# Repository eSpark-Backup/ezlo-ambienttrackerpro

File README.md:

# ezlo-ambienttrackerpro
Convert and do corrections in Ambient Tracker Pro design

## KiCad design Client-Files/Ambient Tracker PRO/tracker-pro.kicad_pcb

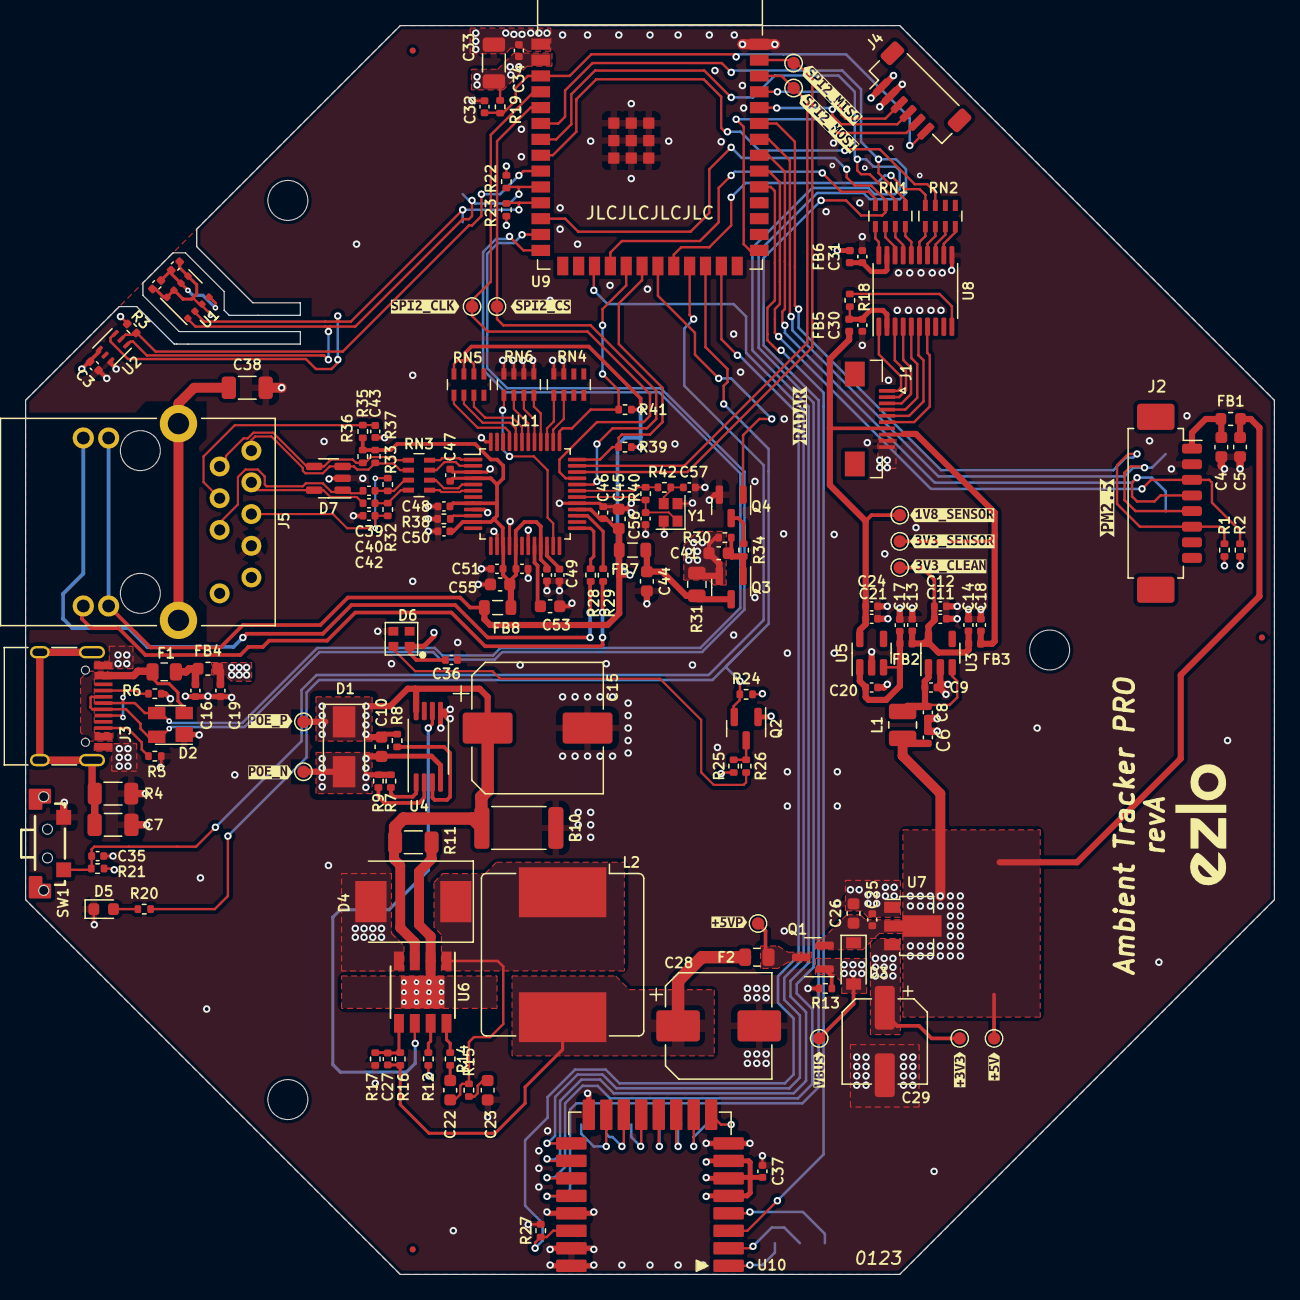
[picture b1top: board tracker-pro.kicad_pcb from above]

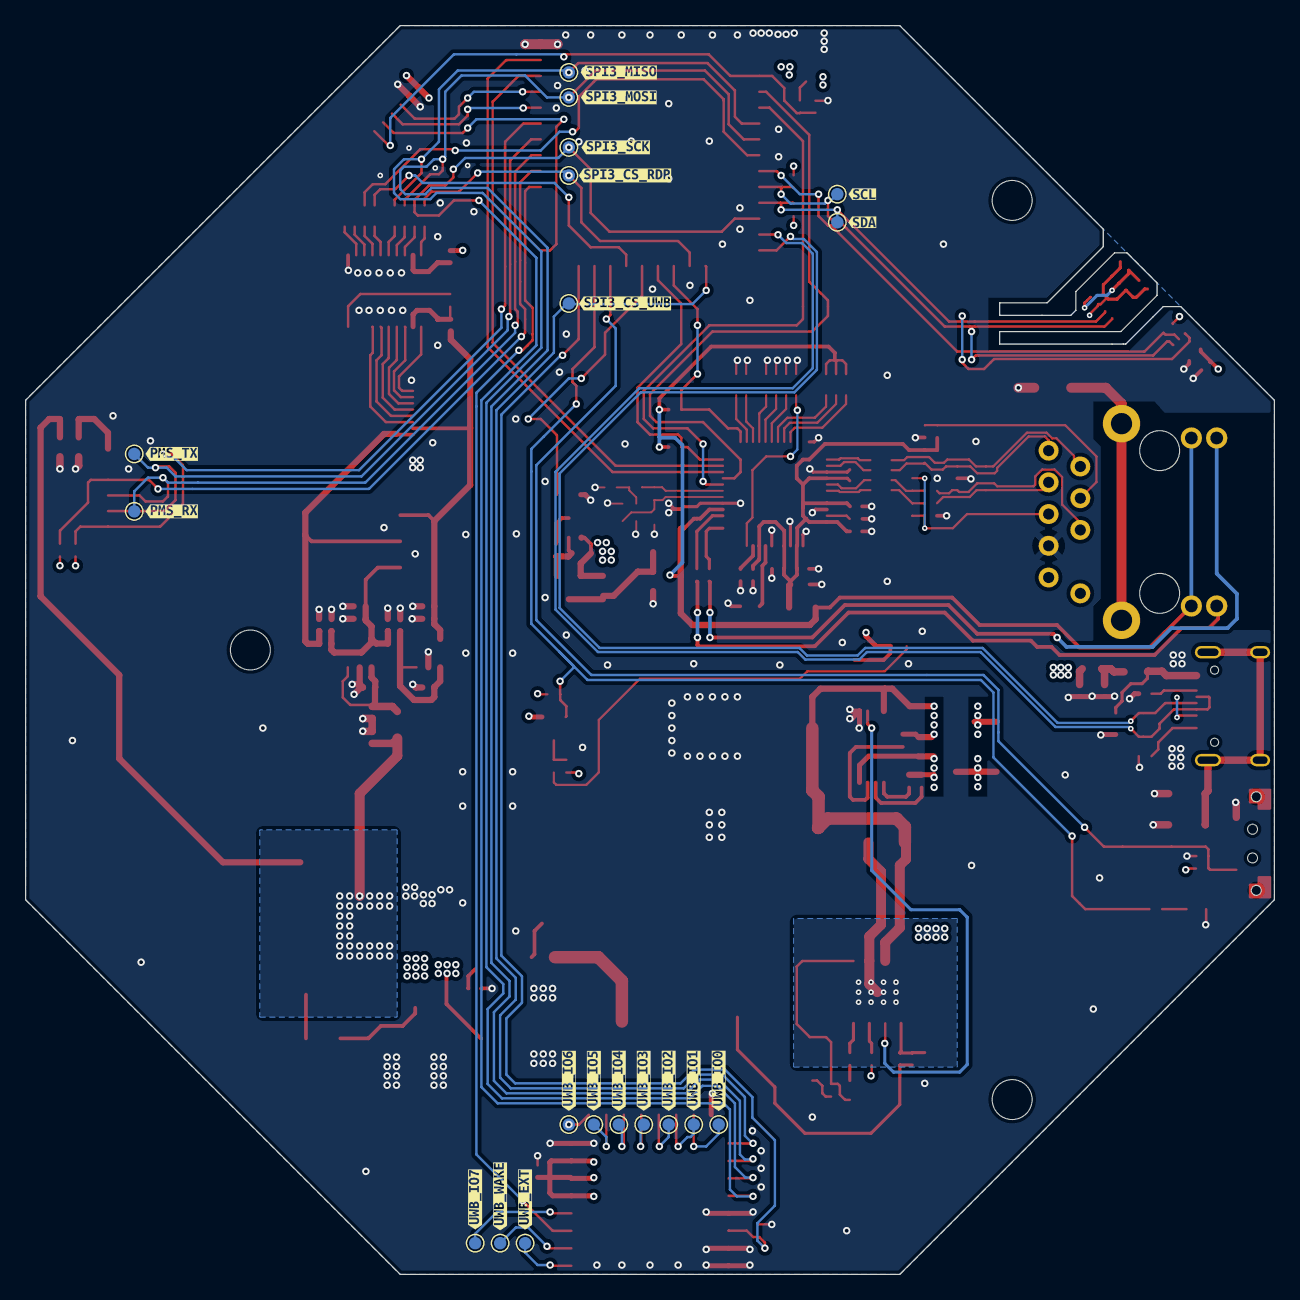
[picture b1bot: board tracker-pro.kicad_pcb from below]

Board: 4 copper layers, 100.0 x 100.0 mm, 220 parts (38 on the bottom side), 128 nets.

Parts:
C1, C2, C9, C11, C13, C14, C18, C19, C20, C21, C25, C30, C31, C34, C35, C36, C37, C46, C47, C48, C50, C51, C52, C54: 0.1uF; C_0402_1005Metric
C3, C32: 1uF; C_0402_1005Metric
C4, C5, C26, C45, C55: 10uF; C_0603_1608Metric
C6, C8, C12, C17, C24: 10uF; C_0402_1005Metric
C7: 4.7nF; C_1206_3216Metric
C10, C22: 0.1uF; C_0603_1608Metric
C15: 15uF; CP_Elec_10x10
C16: 0.01uF; C_0402_1005Metric
C23: 220pF; C_0603_1608Metric
C27, C56, C57: 12pF; C_0402_1005Metric
C28: 470uF; CP_Elec_8x10
C29: 100uF; CP_Elec_6.3x5.8
C33: 22uF; C_1206_3216Metric
C38: 1nF 2KV X7R; C_1206_3216Metric
C39, C40: 6.8nF; C_0402_1005Metric
C41, C44: 22uF; C_0603_1608Metric
C42, C49: 10nF; C_0402_1005Metric
C43: 22nF; C_0402_1005Metric
C53: 4.7uF; C_0603_1608Metric
D1: SMAJ58A; D_SMA
D2: SP0503BAHT; SOT-143
D3: PMEG4030ER; D_SOD-123
D4: SS510; D_SMC
D5: LED_GREEN; LED_0603_1608Metric
D6: SK6812-EC20; sk6812-2020
D7: SP0504BAHT; SOT-23-5
F1, F2: 1A; Fuse_0805_2012Metric
FB1, FB4: BLM18SG121TN1D; L_0603_1608Metric
FB2, FB3, FB5, FB6: BLM15PD121SN1B; L_0402_1005Metric
FB7, FB8: 600R 3A; L_0805_2012Metric
FID1, FID2, FID3: Fiducial; Fiducial_0.5mm_Mask1mm
H1, H2, H3: MountingHole; MountingHole_3.2mm_M3_DIN965
J1: Conn_01x10; AFC01-S10FCC-00_1x10_P0.5mm_Horizontal
J2: PMS5003; Molex_PicoBlade_53261-0871_1x08-1MP_P1.25mm_Horizontal
J3: USB_C_Receptacle_USB2.0; USB_C_Receptacle_HRO_TYPE-C-31-M-12
J4: VoltLink_target; VoltLink-vertical
J5: HanRun_HR873170C
L1: 10uH; L_1008_2520Metric
L2: 33uH 2A; L_Bourns_SRR1208_12.7x12.7mm
N1: Housing; ambient_tracker_pro_revA_enclosure
Q1: SI2323DS; SOT-23
Q2: Si2302CDS; SOT-23
Q3: WPM2015-3; SOT-23
Q4: LMUN2211LT1G; SOT-23
R1, R2, R3, R12, R19, R21, R24, R25, R30, R39, R41: 10K; R_0402_1005Metric
R4: 1M; R_1206_3216Metric
R5, R6: 5K1; R_0402_1005Metric
R7: 180K; R_0402_1005Metric
R8: 24K9; R_0402_1005Metric
R9: 4K42; R_0402_1005Metric
R10: 4K7; R_2512_6332Metric
R11: 0.03R; R_1206_3216Metric
R13, R27: 100K; R_0402_1005Metric
R14: 4R7; R_0402_1005Metric
R15: 22R; R_0402_1005Metric
R16: 300K; R_0402_1005Metric
R17: 57K1; R_0402_1005Metric
R18, R42: 0R; R_0402_1005Metric
R20, R26, R34: 1K; R_0402_1005Metric
R22, R23: 4K7; R_0402_1005Metric
R28, R29: 330R; R_0402_1005Metric
R31: 0R; R_0805_2012Metric
R32, R33, R36, R37: 49R9; R_0402_1005Metric
R35: 10R; R_0402_1005Metric
R38: 12K4; R_0402_1005Metric
R40: 1M; R_0402_1005Metric
RN1, RN2: 0R; R_Array_Concave_4x0603
RN3: 33R; R_Array_Concave_4x0603
RN4, RN5, RN6: 10K; R_Array_Concave_4x0603
SW1: USER; Switch_YTS-B003-2A
TP1: PMS_TX; TestPoint_Pad_D1.0mm
TP2: PMS_RX; TestPoint_Pad_D1.0mm
TP3: POE_P; TestPoint_Pad_D1.0mm
TP4: POE_N; TestPoint_Pad_D1.0mm
TP5: 3V3_C; TestPoint_Pad_D1.0mm
TP6: 3V3_S; TestPoint_Pad_D1.0mm
TP7: VBUS; TestPoint_Pad_D1.0mm
TP8: 1V8_S; TestPoint_Pad_D1.0mm
TP9: +5V; TestPoint_Pad_D1.0mm
TP10: 3V3; TestPoint_Pad_D1.0mm
TP11: 5VP; TestPoint_Pad_D1.0mm
TP12: SCL; TestPoint_Pad_D1.0mm
TP13: SDA; TestPoint_Pad_D1.0mm
TP14: SPI2_MISO; TestPoint_Pad_D1.0mm
TP15: SPI2_MOSI; TestPoint_Pad_D1.0mm
TP16: SPI2_SCK; TestPoint_Pad_D1.0mm
TP17: SPI2_CS; TestPoint_Pad_D1.0mm
TP18: SPI3_MISO; TestPoint_Pad_D1.0mm
TP19: SPI3_MOSI; TestPoint_Pad_D1.0mm
TP20: SPI3_SCK; TestPoint_Pad_D1.0mm
TP21: SPI3_CS_UWB; TestPoint_Pad_D1.0mm
TP22: SPI3_CS_RDR; TestPoint_Pad_D1.0mm
TP23: UWB_EXT; TestPoint_Pad_D1.0mm
TP24: UWB_WAKE; TestPoint_Pad_D1.0mm
TP25: UWB_IO7; TestPoint_Pad_D1.0mm
TP26: UWB_IO6; TestPoint_Pad_D1.0mm
TP27: UWB_IO5; TestPoint_Pad_D1.0mm
TP28: UWB_IO4; TestPoint_Pad_D1.0mm
TP29: UWB_IO3; TestPoint_Pad_D1.0mm
TP30: UWB_IO2; TestPoint_Pad_D1.0mm
TP31: UWB_IO1; TestPoint_Pad_D1.0mm
TP32: UWB_IO0; TestPoint_Pad_D1.0mm
U1: BME680; Bosch_LGA-8_3x3mm_P0.8mm_ClockwisePinNumbering
U2: LTR-303ALS-01; Lite-On_LTR-303ALS-01
U3: XC6228D332VR-G; SOT-23-5
U4: TPS2375PW-1; TSSOP-8_4.4x3mm_P0.65mm
U5: XC6228D182VR-G; SOT-23-5
U6: TX4138; Diodes_SO-8EP
U7: LR1107; SOT-89-3
U8: TXS0108EPWR; TSSOP-20_4.4x6.5mm_P0.65mm
U9: ESP32-S3-WROOM-1-N8R2; ESP32-S3-WROOM-1
U10: DWM3000; Qorvo_DWM3000
U11: W5500; LQFP-48_7x7mm_P0.5mm
V1: EZLO_LOGO; Logo Ezlo_M
Y1: 25Mhz; Crystal_SMD_2016-4Pin_2.0x1.6mm
kibuzzard-63AACF69: G***; kibuzzard-63AACF69
kibuzzard-63AACF76: G***; kibuzzard-63AACF76
kibuzzard-63AACFD0: G***; kibuzzard-63AACFD0
kibuzzard-63AAD0AA: G***; kibuzzard-63AAD0AA
kibuzzard-63AAD00B: G***; kibuzzard-63AAD00B
kibuzzard-63AAD0BE: G***; kibuzzard-63AAD0BE
kibuzzard-63AAD0D4: G***; kibuzzard-63AAD0D4
kibuzzard-63AAD0DC: G***; kibuzzard-63AAD0DC
kibuzzard-63AAD001: G***; kibuzzard-63AAD001
kibuzzard-63AAD1C0: G***; kibuzzard-63AAD1C0
kibuzzard-63AAD1D3: G***; kibuzzard-63AAD1D3
kibuzzard-63AAD1FD: G***; kibuzzard-63AAD1FD
kibuzzard-63AAD2A3: G***; kibuzzard-63AAD2A3
kibuzzard-63AAD2C0: G***; kibuzzard-63AAD2C0
kibuzzard-63AAD2D7: G***; kibuzzard-63AAD2D7
kibuzzard-63AAD02E: G***; kibuzzard-63AAD02E
kibuzzard-63AAD07E: G***; kibuzzard-63AAD07E
kibuzzard-63AAD16B: G***; kibuzzard-63AAD16B
kibuzzard-63AAD19E: G***; kibuzzard-63AAD19E
kibuzzard-63AAD20D: G***; kibuzzard-63AAD20D
kibuzzard-63AAD21C: G***; kibuzzard-63AAD21C
kibuzzard-63AAD27D: G***; kibuzzard-63AAD27D
kibuzzard-63AAD32F: G***; kibuzzard-63AAD32F
kibuzzard-63AAD33F: G***; kibuzzard-63AAD33F
kibuzzard-63AAD039: G***; kibuzzard-63AAD039
kibuzzard-63AAD045: G***; kibuzzard-63AAD045
kibuzzard-63AAD061: G***; kibuzzard-63AAD061
kibuzzard-63AAD088: G***; kibuzzard-63AAD088
kibuzzard-63AAD273: G***; kibuzzard-63AAD273
kibuzzard-63AAD309: G***; kibuzzard-63AAD309
kibuzzard-63AAD314: G***; kibuzzard-63AAD314
kibuzzard-63AAD337: G***; kibuzzard-63AAD337
kibuzzard-63AAD348: G***; kibuzzard-63AAD348
kibuzzard-63AAD350: G***; kibuzzard-63AAD350

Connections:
1V8_SENSOR: C21.1, C24.1, FB5.2, J1.7, TP8.1, U5.5 (VOUT)
3V3_SENSOR: C18.1, FB3.2, J1.8, TP6.1
+3V3: C1.2, C2.1, C3.1, C29.1, C33.2, C34.2, C37.1, C41.1, FB6.1, J4.1 (3V3), Q2.1 (G), Q3.2 (S), R1.1, R2.1, R3.1, R12.2, R19.2, R21.2, R22.2, R23.2, R24.1, R30.2, R31.1, TP10.1, U1.2 (CSB), U1.5 (SDO), U1.6 (VDDIO), U1.8 (VDD), U2.1 (VDD), U7.3 (VOUT), U9.2 (3V3), U10.5 (VDD1), U10.6 (VDD3V3), U10.7 (VDD3V3)
+5V: C5.1, C6.1, C25.1, C26.1, C36.1, D3.1 (K), D6.1 (VDD), FB1.2, L1.1, Q1.2 (S), R25.1, TP9.1, U7.2 (VIN)
+5VP: F2.1, Q1.3 (D), TP11.1
/ESP32/DIN1: D6.4 (DIN), R26.2
/ESP32/EN: C32.1, J4.6 (EN), R19.1, U9.3 (EN)
/ESP32/GPIO13: Q4.1 (B), U9.21 (GPIO13)
/ESP32/GPIO14: RN2.4 (R4.1), U9.22 (GPIO14)
/ESP32/GPIO15: RN2.3 (R3.1), U9.8 (GPIO15)
/ESP32/GPIO21: C35.1, R21.1, SW1.1, U9.23 (GPIO21)
/ESP32/GPIO47: Q2.2 (S), R20.1, R24.2, U9.24 (GPIO47)
/ESP32/IO0: J4.5 (IO0), U9.27 (GPIO0/BOOT)
/ESP32/RXD: J4.4 (RXD), U9.36 (U0RXD/GPIO44)
/ESP32/SCL: R22.1, TP12.1, U1.4 (SCK), U2.4 (SCL), U9.10 (GPIO17)
/ESP32/SDA: R23.1, TP13.1, U1.3 (SDI), U2.6 (SDA), U9.11 (GPIO18)
/ESP32/SPI2_CS: TP17.1, U9.5 (GPIO5), U11.32 (~SCS)
/ESP32/SPI2_MISO: TP14.1, U9.39 (GPIO1), U11.34 (MISO)
/ESP32/SPI2_MOSI: TP15.1, U9.38 (GPIO2), U11.35 (MOSI)
/ESP32/SPI2_SCK: TP16.1, U9.4 (GPIO4), U11.33 (SCLK)
/ESP32/SPI3_CS_RDR: RN1.4 (R4.1), TP22.1, U9.18 (GPIO10)
/ESP32/SPI3_CS_UWB: TP21.1, U9.17 (GPIO9), U10.17 (CS)
/ESP32/SPI3_MISO: RN1.1 (R1.1), TP18.1, U9.6 (GPIO6), U10.19 (MISO)
/ESP32/SPI3_MOSI: RN1.2 (R2.1), TP19.1, U9.7 (GPIO7), U10.18 (MOSI)
/ESP32/SPI3_SCK: RN1.3 (R3.1), TP20.1, U9.12 (GPIO8), U10.20 (SCLK)
/ESP32/TXD: J4.3 (TXD), U9.37 (U0TXD/GPIO43)
/Ethernet/1V2O: C49.1, U11.22 (1V2O)
/Ethernet/ACTLED: R29.2, U11.27 (ACTLED)
/Ethernet/EXRES1: R38.2, U11.10 (EXRES1)
/Ethernet/LAN_ACT: J5.14, R29.1
/Ethernet/LAN_CT_R: C42.1, J5.5, R32.2, R33.2
/Ethernet/LAN_CT_T: C43.1, J5.4, R35.2
/Ethernet/LAN_LINK: J5.12, R28.1
/Ethernet/LAN_PWR_N: C10.2, D1.2 (A), J5.10, R7.2, R9.2, TP4.1, U4.4 (VSS)
/Ethernet/LAN_RD_N: C39.1, D7.1 (K), J5.6
/Ethernet/LAN_RD_P: C40.1, D7.5 (K), J5.3
/Ethernet/LAN_TD_N: D7.4 (K), J5.2, R36.2, RN3.5 (R4.2)
/Ethernet/LAN_TD_P: D7.3 (K), J5.1, R37.2, RN3.6 (R3.2)
/Ethernet/LINKLED: R28.2, U11.25 (LINKLED)
/Ethernet/PMODE0: RN5.1 (R1.1), U11.45 (PMODE0)
/Ethernet/PMODE1: RN5.2 (R2.1), U11.44 (PMODE1)
/Ethernet/PMODE2: RN5.3 (R3.1), U11.43 (PMODE2)
/Ethernet/RJ45_SHIELD: C38.1, J5.15 (SHIELD), J5.16 (SHIELD)
/Ethernet/TOCAP: C53.1, U11.20 (TOCAP)
/Ethernet/W5500_3V3: C44.1, FB7.1, Q3.3 (D), R31.2
/Ethernet/W5500_INT: R39.1, U9.20 (GPIO12), U11.36 (~INT)
/Ethernet/W5500_RST: R41.1, U9.19 (GPIO11), U11.37 (~RST)
/Ethernet/W5500_RX_N: RN3.2 (R2.1), U11.5 (RXN)
/Ethernet/W5500_RX_P: RN3.1 (R1.1), U11.6 (RXP)
/Ethernet/W5500_TX_N: RN3.4 (R4.1), U11.1 (TXN)
/Ethernet/W5500_TX_P: RN3.3 (R3.1), U11.2 (TXP)
/Ethernet/W5500_XI: C56.1, R40.1, U11.30 (XI/CLKIN), Y1.1
/Ethernet/W5500_XO: R40.2, R42.2, U11.31 (XO)
/Level shifter/SPI_OE: R18.1, U8.10 (OE)
/Level shifter/VCCA: C30.1, FB5.1, R18.2, U8.2 (VCCA)
/Level shifter/VCCB: C31.1, FB6.2, U8.19 (VCCB)
/Power-Interface/3V3_CLEAN: C11.1, C12.1, C13.1, C14.1, FB2.1, FB3.1, TP5.1, U3.5 (VOUT)
/Power-Interface/3V3_LDO1V8: C17.1, C20.1, FB2.2, U5.1 (VIN), U5.3 (CE)
/Power-Interface/CC1: J3.A5 (CC1), R6.1
/Power-Interface/CC2: J3.B5 (CC2), R5.1
/Power-Interface/DCDC_BS: R14.2, U6.8 (BS)
/Power-Interface/DCDC_FB: C27.2, R16.1, R17.2, U6.5 (FB)
/Power-Interface/DCDC_ILIM: R11.1, U6.2 (ILIM), U6.9 (ILIM)
/Power-Interface/DCDC_OUT: C27.1, C28.1, F2.2, L2.2, R16.2
/Power-Interface/DCDC_POK: R12.1, U6.7 (POK)
/Power-Interface/DCDC_SW: C22.2, D4.1 (K), L2.1, R15.2, U6.1 (SW)
/Power-Interface/DCDC_VIN: C10.1, C15.1, D1.1 (K), J5.9, R8.1, R10.2, R11.2, TP3.1, U4.8 (VDD), U6.3 (VIN)
/Power-Interface/POE_EN_DCDC: U4.6 (PG), U6.6 (EN)
/Power-Interface/USB_D_N: D2.4 (K), J3.A7 (D-), J3.B7 (D-), U9.13 (GPIO19/USB_D-)
/Power-Interface/USB_D_P: D2.3 (K), J3.A6 (D+), J3.B6 (D+), U9.14 (GPIO20/USB_D+)
/Power-Interface/VIN_CLEAN: C8.1, C9.1, L1.2, U3.1 (VIN), U3.3 (CE)
/Power-Interface/V_USB: D2.2 (K), F1.2, J3.A4 (VBUS), J3.A9 (VBUS), J3.B4 (VBUS), J3.B9 (VBUS)
/Sensors/BGT_CLK: J1.2, U8.3 (A2)
/Sensors/BGT_CS: J1.1, U8.1 (A1)
/Sensors/BGT_IRQ: J1.6, U8.7 (A6)
/Sensors/BGT_MISO: J1.4, U8.5 (A4)
/Sensors/BGT_MOSI: J1.3, U8.4 (A3)
/Sensors/BGT_RST: J1.5, U8.6 (A5)
/Sensors/INT_ALS: R3.2, U2.5 (INT), U9.9 (GPIO16)
/Sensors/PMS_5V: C4.1, FB1.1, J2.1
/Sensors/PMS_RST: J2.6, R1.2, U9.35 (TMS/GPIO42)
/Sensors/PMS_RX: J2.4, TP2.1, U9.33 (TDO/GPIO40)
/Sensors/PMS_SET: J2.3, R2.2, U9.32 (TCK/GPIO39)
/Sensors/PMS_TX: J2.5, TP1.1, U9.34 (TDI/GPIO41)
/UWB/UWB_IRQ: R27.1, U9.25 (GPIO48), U10.22 (IO8/IRQ)
/UWB/UWB_RST: U9.31 (GPIO38), U10.3 (~RST)
GND: C1.1, C2.2, C3.2, C4.2, C5.2, C6.2, C7.2, C8.2, C9.2, C11.2, C12.2, C13.2, C14.2, C15.2, C16.2, C17.2, C18.2, C19.2, C20.2, C21.2, C23.1, C24.2, C25.2, C26.2, C28.2, C29.2, C30.2, C31.2, C32.2, C33.1, C34.1, C35.2, C36.2, C37.2, C38.2, C42.2, C43.2, C44.2, C45.2, C46.2, C47.2, C48.2, C49.2, C50.2, C51.2, C52.2, C53.2, C54.2, C55.2, C56.2, C57.2, D2.1 (A), D4.2 (A), D5.1 (K), D6.3 (VSS), D7.2 (A), J1.9, J1.10, J2.2, J3.A1 (GND), J3.A12 (GND), J3.B1 (GND), J3.B12 (GND), J4.2 (GND), J5.7, Q4.2 (E), R4.2, R5.2, R6.2, R10.1, R13.2, R17.1, R27.2, R38.1, RN4.3 (R3.1), RN4.4 (R4.1), RN6.1 (R1.1), RN6.2 (R2.1), RN6.3 (R3.1), RN6.4 (R4.1), SW1.2, U1.1 (GND), U1.7 (GND), U2.3 (GND), U3.2 (GND), U4.5 (RTN), U5.2 (GND), U6.4 (GND), U7.1 (GND), U8.11 (GND), U9.1 (GND), U9.40 (GND), U9.41 (GND), U10.8 (GND), U10.16 (GND), U10.21 (GND), U10.23 (GND), U10.24 (GND), U11.3 (AGND), U11.9 (AGND), U11.14 (AGND), U11.16 (AGND), U11.19 (AGND), U11.29 (GND), U11.48 (AGND), Y1.2, Y1.4
unnamed: C7.1, J3.S1 (SHIELD), R4.1
unnamed: C16.1, F1.1, FB4.1
unnamed: C22.1, R14.1
unnamed: C23.2, R15.1
unnamed: C39.2, R33.1, RN3.7 (R2.2)
unnamed: C40.2, R32.1, RN3.8 (R1.2)
unnamed: C41.2, Q3.1 (G), R30.1, R34.1
unnamed: C57.1, R42.1, Y1.3
unnamed: D5.2 (A), R20.2
unnamed: Q2.3 (D), R25.2, R26.1
unnamed: Q4.3 (C), R34.2
unnamed: R7.1, U4.1 (ILIM)
unnamed: R8.2, U4.3 (DET)
unnamed: R9.1, U4.2 (CLASS)
unnamed: RN1.5 (R4.2), U8.20 (B1)
unnamed: RN1.6 (R3.2), U8.18 (B2)
unnamed: RN1.7 (R2.2), U8.17 (B3)
unnamed: RN1.8 (R1.2), U8.16 (B4)
unnamed: RN2.5 (R4.2), U8.15 (B5)
unnamed: RN2.6 (R3.2), U8.14 (B6)
unnamed: RN2.7 (R2.2), U8.13 (B7)
unnamed: RN2.8 (R1.2), U8.12 (B8)
unnamed: RN4.5 (R4.2), U11.39 (RSVD)
unnamed: RN4.6 (R3.2), U11.38 (RSVD)
unnamed: RN6.5 (R4.2), U11.23 (RSVD)
unnamed: RN6.6 (R3.2), U11.42 (RSVD)
unnamed: RN6.7 (R2.2), U11.41 (RSVD)
unnamed: RN6.8 (R1.2), U11.40 (RSVD)
unnamed: TP23.1, U10.1 (EXTON)
unnamed: TP24.1, U10.2 (WAKEUP)
unnamed: TP25.1, U10.4 (IO7/SYNC)
unnamed: TP26.1, U10.9 (IO6/SPIPHA)
unnamed: TP27.1, U10.10 (IO5/SPIPOL)
unnamed: TP28.1, U10.11 (IO4)
unnamed: TP29.1, U10.12 (IO3/TXLED)
unnamed: TP30.1, U10.13 (IO2/RXLED)
unnamed: TP31.1, U10.14 (IO1/SFDLED)
unnamed: TP32.1, U10.15 (IO0/RXOKLED)
VBUS: C19.1, D3.2 (A), FB4.2, Q1.1 (G), R13.1, TP7.1
VDD: C45.1, C46.1, FB7.2, FB8.1, J5.11, J5.13, R39.2, R41.2, RN5.6 (R3.2), RN5.7 (R2.2), RN5.8 (R1.2), U11.28 (VDD)
VDDA: C47.1, C48.1, C50.1, C51.1, C52.1, C54.1, C55.1, FB8.2, R35.1, R36.1, R37.1, U11.4 (AVDD), U11.8 (AVDD), U11.11 (AVDD), U11.15 (AVDD), U11.17 (AVDD), U11.21 (AVDD)

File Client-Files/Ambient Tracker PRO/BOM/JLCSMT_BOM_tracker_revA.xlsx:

Comment | Designator | Footprint | LCSC Part #（optional）
0.1uF | C1, C2, C9, C11, C13, C14, C16, C18, C19, C20, C21, C25, C30, C31, C34, C35, C3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 | Capacitor_SMD:C_0402_1005Metric | C307331
1uF | C3, C32, | Capacitor_SMD:C_0402_1005Metric | C52923
10uF | C4, C5, C26, C45, C55, | Capacitor_SMD:C_0603_1608Metric | C92487
10uF | C6, C8, C12, C17, C24, | Capacitor_SMD:C_0402_1005Metric | C315248
4.7nF | C7, | Capacitor_SMD:C_1206_3216Metric | C107198
0.1uF | C10, C22, | Capacitor_SMD:C_0603_1608Metric | C15725
15uF | C15, | Capacitor_SMD:CP_Elec_10x10 | C473415
220pF | C23, | Capacitor_SMD:C_0603_1608Metric | DNP | C472787
12pF | C27, C56, C57, | Capacitor_SMD:C_0402_1005Metric | C1547
470uF | C28, | Capacitor_SMD:CP_Elec_8x10 | C164069
100uF | C29, | Capacitor_SMD:CP_Elec_6.3x5.8 | C340720
22uF | C33, | Capacitor_SMD:C_1206_3216Metric | C408152
1nF 2KV X7R | C38, | Capacitor_SMD:C_1206_3216Metric | C23631
6.8nF | C39, C40, | Capacitor_SMD:C_0402_1005Metric | C307331
22uF | C41, C44, | Capacitor_SMD:C_0603_1608Metric | C59461
10nF | C42, C49, | Capacitor_SMD:C_0402_1005Metric | C307331
22nF | C43, | Capacitor_SMD:C_0402_1005Metric | C307331
4.7uF | C53, | Capacitor_SMD:C_0603_1608Metric | C19666
SMAJ58A | D1, | Diode_SMD:D_SMA | C320541
SP0503BAHT | D2, | Package_TO_SOT_SMD:SOT-143 | C2682275
PMEG4030ER | D3, | Diode_SMD:D_SOD-123 | C389355
SS510 | D4, | Diode_SMD:D_SMC | C717458
LED_GREEN | D5, | LED_SMD:LED_0603_1608Metric | C84267
SK6812-EC20 | D6, | Ezlo:sk6812-2020 | C2909058
SP0504BAHT | D7, | Package_TO_SOT_SMD:SOT-23-5 | C2827708
1A | F1, F2, | Fuse:Fuse_0805_2012Metric | C369152
BLM18SG121TN1D | FB1, FB4, | Inductor_SMD:L_0603_1608Metric | C113030
BLM15PD121SN1B | FB2, FB3, FB5, FB6, | Inductor_SMD:L_0402_1005Metric | C76891
600R 3A | FB7, FB8, | Inductor_SMD:L_0805_2012Metric | C139168
Conn_01x10 | J1, | Ezlo:AFC01-S10FCC-00_1x10_P0.5mm_Horizontal | C262266
USB_C_Receptacle_USB2.0 | J3, | Ezlo:USB_C_Receptacle_HRO_TYPE-C-31-M-12 | C165948
VoltLink_target | J4, | Voltlog:VoltLink-vertical | C145963
10uH | L1, | Inductor_SMD:L_1008_2520Metric | C88532
33uH 2A | L2, | Inductor_SMD:L_Bourns_SRR1208_12.7x12.7mm | C2929502
SI2323DS | Q1, | Package_TO_SOT_SMD:SOT-23 | C693130
Si2302CDS | Q2, | Package_TO_SOT_SMD:SOT-23 | C10488
WPM2015-3 | Q3, | Package_TO_SOT_SMD:SOT-23 | C5246393
LMUN2211LT1G | Q4, | Package_TO_SOT_SMD:SOT-23 | C12775
10K | R1, R2, R3, R12, R19, R21, R24, R25, R30, R39, R41, | Resistor_SMD:R_0402_1005Metric | C25744
1M | R4, | Resistor_SMD:R_1206_3216Metric | C17927
5K1 | R5, R6, | Resistor_SMD:R_0402_1005Metric | C25905
180K | R7, | Resistor_SMD:R_0402_1005Metric | C284388
24K9 | R8, | Resistor_SMD:R_0402_1005Metric | C25874
4K42 | R9, | Resistor_SMD:R_0402_1005Metric | C517779
4K7 | R10, | Resistor_SMD:R_2512_6332Metric | C473645
0.03R | R11, | Resistor_SMD:R_1206_3216Metric | C473665
100K | R13, R27, | Resistor_SMD:R_0402_1005Metric | C25741
4R7 | R14, | Resistor_SMD:R_0402_1005Metric | C25169
22R | R15, | Resistor_SMD:R_0402_1005Metric | DNP | C25092
301K | R16, | Resistor_SMD:R_0402_1005Metric | C226978
57K6 | R17, | Resistor_SMD:R_0402_1005Metric | C26983
0R | R18, R42, | Resistor_SMD:R_0402_1005Metric | C17168
1K | R26, R34, | Resistor_SMD:R_0402_1005Metric | C25905
1K | R20 | Resistor_SMD:R_0402_1005Metric | DNP
4K7 | R22, R23, | Resistor_SMD:R_0402_1005Metric | C25900
330R | R28, R29, | Resistor_SMD:R_0402_1005Metric | C25104
0R | R31, | Resistor_SMD:R_0805_2012Metric | DNP | C17477
49R9 | R32, R33, R36, R37, | Resistor_SMD:R_0402_1005Metric | C25120
10R | R35, | Resistor_SMD:R_0402_1005Metric | C25077
12K4 | R38, | Resistor_SMD:R_0402_1005Metric | C11692
1M | R40, | Resistor_SMD:R_0402_1005Metric | C26083
0R | RN1, RN2, | Resistor_SMD:R_Array_Concave_4x0603 | C327053
33R | RN3, | Resistor_SMD:R_Array_Concave_4x0603 | C309681
10K | RN4, RN5, RN6, | Resistor_SMD:R_Array_Concave_4x0603 | C110924
USER | SW1, | Ezlo:Switch_YTS-B003-2A | C2910695
BME680 | U1, | Package_LGA:Bosch_LGA-8_3x3mm_P0.8mm_ClockwisePinNumbering | C125972
LTR-303ALS-01 | U2, | OptoDevice:Lite-On_LTR-303ALS-01 | C364577
XC6228D332VR-G | U3, | Package_TO_SOT_SMD:SOT-23-5 | C69841
TPS2375PW-1 | U4, | Package_SO:TSSOP-8_4.4x3mm_P0.65mm | C202190
XC6228D182VR-G | U5, | Package_TO_SOT_SMD:SOT-23-5 | C216644
TX4138 | U6, | Package_SO:Diodes_SO-8EP | C329267
LR1107 | U7, | Package_TO_SOT_SMD:SOT-89-3 | C171498
TXS0108EPWR | U8, | Package_SO:TSSOP-20_4.4x6.5mm_P0.65mm | C17206
ESP32-S3-WROOM-1-N8R2 | U9, | Espressif:ESP32-S3-WROOM-1 | C2913204
DWM3000 | U10, | Ezlo:Qorvo_DWM3000 | C5299931
W5500 | U11, | Package_QFP:LQFP-48_7x7mm_P0.5mm | C32843
25Mhz | Y1, | Crystal:Crystal_SMD_2016-4Pin_2.0x1.6mm | C255883

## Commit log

2023-11-03 gitignore, client files added
2023-11-03 Branch and files added
2023-11-06 #1 Schematic In Progress.
2023-11-13 #1 Schematic completed.
2023-11-14 #1 Power sheet C2 and C5 value changed
2023-11-16 #2 Schematic Completed.
2023-11-16 #1 Library source changed from "eSpark Centralized" to "eSpark Libraries"
2023-11-16 #3 Placement started
2023-11-17 #1 Designators assigned in POE circuitry. Capacitor and Resistor net assigned to USB shield pins.
2023-11-17 #3 Placement in progress
2023-11-17 #5 eSpark BOM In Progress
2023-11-20 #3 Placement completed.
2023-11-20 #1 Switch debounce cap and pull up resistor had no connection with the switch. Corrected.
2023-11-21 #3 Routing in progress
2023-11-22 #3 Routing almost done. PWR, GND, DRC and Overlays remaining.
2023-11-23 #3 DRC rermaining
2023-11-24 #3 Routing done. It just needs a review from my side.
2023-11-27 #4 Placement and Designing in progress!
2023-11-28 #1 SW1 part changed
2023-11-28 #4 Routing completed. PCB needs verification with the enclosure
2023-11-28 #3 POE circuitry need to be moved downwards as they are colliding with the PMS in the enclosure.
2023-11-29 #3 POE components moved as they were colliding with the PMS sensor.
